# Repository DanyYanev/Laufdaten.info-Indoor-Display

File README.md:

# Laufdaten.info Dust Sensor Indoor Display
Add-on indoor display for your [**laufdaten dust sensor**](https://luftdaten.info/en/home-en/)

If you are contributing to the [**luftdaten.info**](https://luftdaten.info/en/home-en/) project you can build your own indoor weather station and fetch the data off your outdoor sensor.
# How it works
Outside sensor sends information to the Laufdaten servers and to the indoor controller API that displays it on display by your choice. The display controller is connected to your local network with static IP configured from the .ino file (default 192.168.0.50).
The same IP Address you have to add in the outside sensor to send data to the indoor display controller. (More on that in the Configuration Tab) 

*Screenshots from 2.8"(background actually is black)*

# Getting Started
You will need:
  - Working [Laufdaten dust sensor](https://luftdaten.info/en/construction-manual/) **with BME 280 and SDS011**
  - *Another* NodeMCU v3 ESP8266 or ESP-12E
  - *Another* BME 280
  - A display
    - OLED 0.96" I2C interface
    - OLED 1.3" I2C interface
    - LCD TFT 1.44" SPI interface
    - LCD TFT 2.8"  SPI interface with touch
    - LCD TFT 2.8"  SPI interface without touch
    
## Installing
  ##### Setting up the arduino IDE
  - Install the [Arduino IDE](https://www.arduino.cc/en/Main/Software)
  - Add ESP8266 Libraries
    To begin, we’ll need to update the board manager with a custom URL. Open up Arduino, then go to the Preferences (File > Preferences).       Then, towards the bottom of the window, copy this URL into the “Additional Board Manager URLs” text box:

     > http://arduino.esp8266.com/stable/package_esp8266com_index.json
   - Install the following libraries
      - [WifiManager by Ken Taylor](https://github.com/kentaylor/WiFiManager)
      - [Adafruit Sensors](https://github.com/adafruit/Adafruit_Sensor)
      - [Adafruit BME280](https://github.com/adafruit/Adafruit_BME280_Library)
      - LCD
        - [TFT_eSPI by Bodmer](https://github.com/Bodmer/TFT_eSPI)
      - OLED
        - [Driver library for the SSD1306 and SH1106 OLED by ThingPulse](https://github.com/ThingPulse/esp8266-oled-ssd1306)
        
  ##### Connect the hardware for Oled and LCD 1.44"
  - BME280 (I2C)
    - SDA -> D1
    - SDL -> D2
  - OLED (I2C)
    - SDA -> D1
    - SDL -> D2
  - LCD (SPI)
    - TFT_CS -> D8
    - TFT_DC -> D0
    - TFT_RST -> Reset pin
    - TFT_SCL -> D5
    - TFT_SDA -> D7
    - TFT_LED -> +3.3v
    - Make the appropriate changes to User_Setup.h in Bodmer library (by default on Windowns located in Documents/Arduino/libraries/TFT-eSPI/) according to your display. The User_Setup.h file is very well documented.
    - You can find ready User_Setup.h in code folders. For 1.44 if you have screen offset choose different board.
            
  - Buttons (Pin to GND)
    - D6 (Display page changing)
    - D3 (Configuration Mode -Onboard flash button)
  - You can look also schematic pdf in shields folder
  
  ##### Connect the hardware for LCD 2.80"
  - See schematic pdf in shields folder
  
##### Configure the Indoor Display Conroller
  - After uploading the code the controller will run in Configuration Mode automatically. To manually put the controller in config mode use the flash button. 
  - The device tries to connect to the configured WLAN access point. If this does not work, the controller opens an access point with the name "ESP *id*". The ID referes to the ChipID (ex. ESP12345). Connect to the new network, wait a moment until the connection is made. Sometimes it take multiple attempts.
  - Configure using browser
    - Open your browser and type in http://192.168.4.1/. You see the menu site, choose “Configure” and input your credentional.
    - After saving the desired configuration click on **EXIT PORTAL**! Else the configuration won't be saved.
  **OR**
  - Configure using android application. Special thanks to Keneth Taylor.
    - Download the [ESP Connect app](https://play.google.com/store/apps/details?id=au.com.umranium.espconnect) and follow the steps.
  - Oled version is without WiFi menager and you must add wifi SSID and Password in the code.  
  
##### Configure the OutsideSensor
  - Find laufdatens sensor IP Address.
  - Go to its IP Address (ex. 192.168.0.112)
  - Click on Configuration
  - Add the static IP of the indoor display controller 192.168.0.50, (standart router settings from 192.168.0.2 through 192.168.0.99 are not used for DHCP).
  - The path and the port as shown below.

## Shields
  - Kicad and Gerber files are in shields folder.
    - Indoor display
      - Oled 0.96 (Tested)
      - LCD 1.44  (Tested)
      - LCD 2.80  (ESP-12E tested)
      - LCD 2.80  (NodeMCU not tested)
    - Outdoor sensor for better connection between sensors and ESP.

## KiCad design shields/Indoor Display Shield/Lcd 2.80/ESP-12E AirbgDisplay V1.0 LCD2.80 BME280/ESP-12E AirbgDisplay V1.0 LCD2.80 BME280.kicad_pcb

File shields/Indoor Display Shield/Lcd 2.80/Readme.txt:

Buttons on D2 and D6 are not used with touchscreen.
Led on D4 duplicate led on ESP.
PCB can be use with another sensors for air quality BME680 or CCS811.

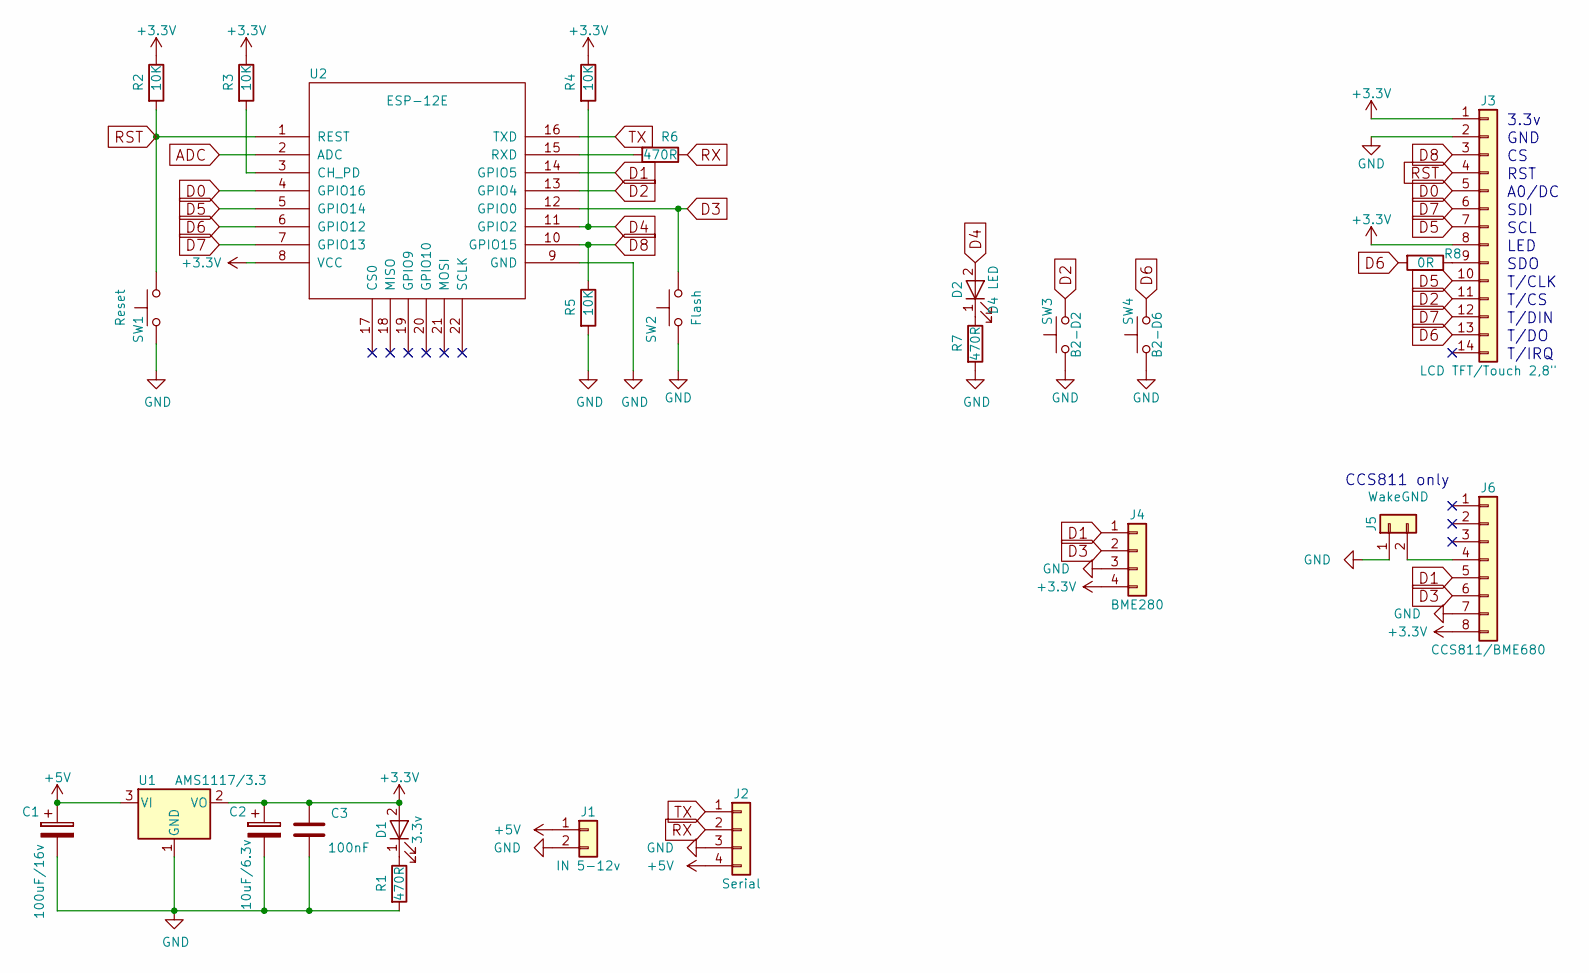
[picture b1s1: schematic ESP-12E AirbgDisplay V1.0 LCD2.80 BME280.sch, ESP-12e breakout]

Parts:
C1: 100uF/16v; C_1812_HandSoldering
C2: 10uF/6.3v; C_1206_HandSoldering
C3: 100nF; C_1206_HandSoldering
D1: 3.3v; LED_1206_HandSoldering
D2: D4 LED; LED_1206_HandSoldering
J1: IN 5-12v; Pin_Header_Straight_1x02_Pitch2.54mm
J2: Serial; Pin_Header_Angled_1x04_Pitch2.54mm
J3: LCD TFT/Touch 2,8\"; Pin_Header_Straight_1x14_Pitch2.54mm
J4: BME280; Pin_Header_Straight_1x04_Pitch2.54mm
J5: WakeGND; Pin_Header_Straight_1x02_Pitch2.54mm
J6: CCS811/BME680; Pin_Header_Straight_1x08_Pitch2.54mm
R1, R6, R7: 470R; R_1206_HandSoldering
R2, R3, R4, R5: 10K; R_1206_HandSoldering
R8: 0R; R_1206_HandSoldering
SW1: Reset; SW_SPST_FSMSM
SW2: Flash; SW_SPST_FSMSM
SW3: B2-D2; SW_SPST_FSMSM
SW4: B2-D6; SW_SPST_FSMSM
U1: AMS1117/3.3; SOT-223-3_TabPin2
U2: ESP-12E; ESP-12E_SMD

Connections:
+3V3: C2.1, C3.1, D1.2 (A), J3.1, J3.8, J4.4, J6.8, R2.1, R3.1, R4.1, U1.2 (VO), U2.8 (VCC)
+5V: C1.1, J1.1, J2.4, U1.3 (VI)
ADC: U2.2 (ADC)
D0: J3.5, U2.4 (GPIO16)
D1: J4.1, J6.5, U2.14 (GPIO5)
D2: J3.11, SW3.2, U2.13 (GPIO4)
D3: J4.2, J6.6, SW2.2, U2.12 (GPIO0)
D4: D2.2 (A), R4.2, U2.11 (GPIO2)
D5: J3.7, J3.10, U2.5 (GPIO14)
D6: J3.13, R8.2, SW4.2, U2.6 (GPIO12)
D7: J3.6, J3.12, U2.7 (GPIO13)
D8: J3.3, R5.1, U2.10 (GPIO15)
GND: C1.2, C2.2, C3.2, J1.2, J2.3, J3.2, J4.3, J5.1, J6.7, R1.2, R5.2, R7.2, SW1.1, SW2.1, SW3.1, SW4.1, U1.1 (GND), U2.9 (GND)
unnamed: D1.1 (K), R1.1
unnamed: D2.1 (K), R7.1
unnamed: J3.9, R8.1
unnamed: J5.2, J6.4
unnamed: R3.2, U2.3 (CH_PD)
unnamed: R6.2, U2.15 (RXD)
RST: J3.4, R2.2, SW1.2, U2.1 (REST)
RX: J2.2, R6.1
TX: J2.1, U2.16 (TXD)

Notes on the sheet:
3.3v
GND
RST
A0/DC
SDI
SCL
LED
SDO
T/CLK
T/CS
T/DIN
T/DO
T/IRQ
CCS811 only

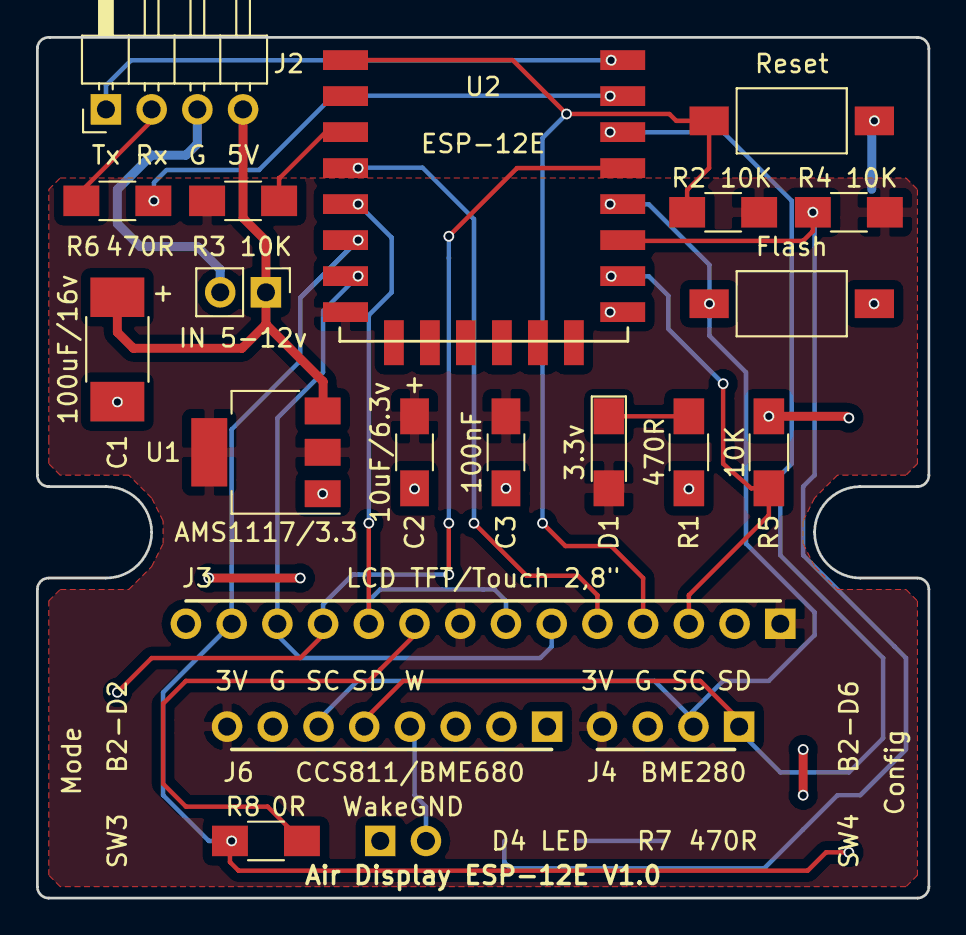
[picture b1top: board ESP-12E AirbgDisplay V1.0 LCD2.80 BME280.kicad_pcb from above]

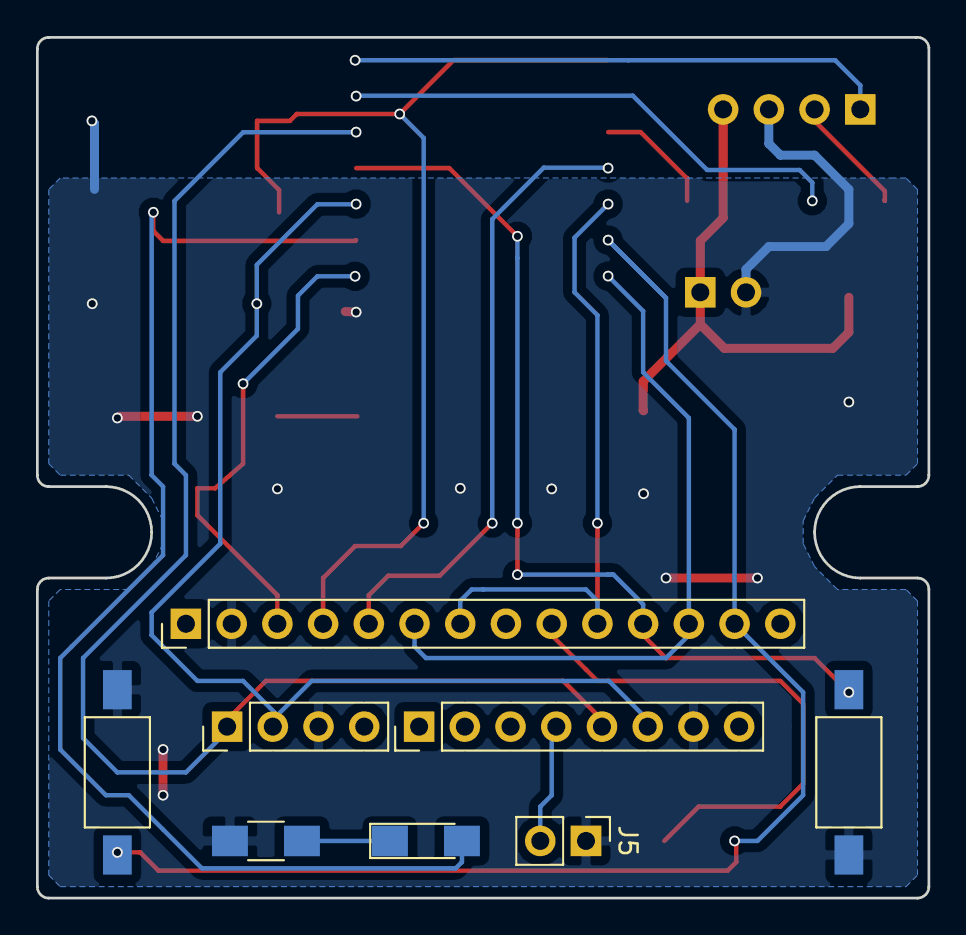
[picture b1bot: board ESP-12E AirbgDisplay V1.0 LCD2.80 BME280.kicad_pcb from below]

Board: 2 copper layers, 49.5 x 47.8 mm, 25 parts (8 on the bottom side), 21 nets.

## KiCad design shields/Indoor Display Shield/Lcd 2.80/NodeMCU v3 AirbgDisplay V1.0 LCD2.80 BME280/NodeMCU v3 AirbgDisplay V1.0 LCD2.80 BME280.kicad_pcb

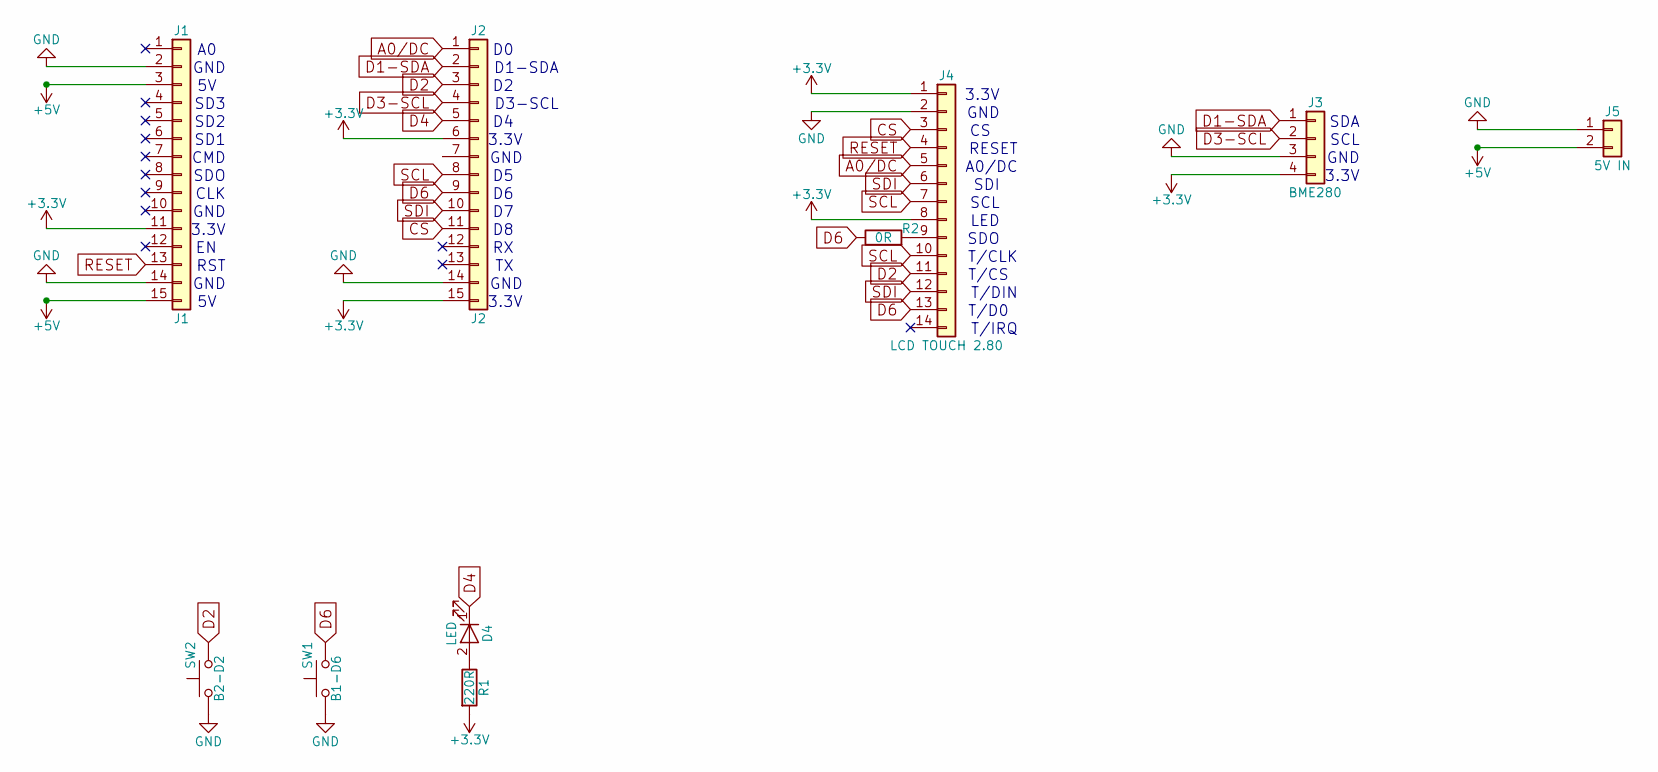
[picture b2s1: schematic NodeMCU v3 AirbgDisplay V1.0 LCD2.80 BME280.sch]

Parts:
D4: LED; LED_1206_HandSoldering
J1: J1; Pin_Header_Straight_1x15_Pitch2.54mm
J2: J2; Pin_Header_Straight_1x15_Pitch2.54mm
J3: BME280; Pin_Header_Straight_1x04_Pitch2.54mm
J4: LCD TOUCH 2.80; Pin_Header_Straight_1x14_Pitch2.54mm
J5: 5V IN; JST_XH_S02B-XH-A_02x2.50mm_Angled
R1: 220R; R_1206_HandSoldering
R2: 0R; R_1206_HandSoldering
SW1: B1-D6; SW_PUSH_6mm_h5mm
SW2: B2-D2; SW_PUSH_6mm_h5mm

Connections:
+3V3: J1.11, J2.6, J2.15, J3.4, J4.1, J4.8, R1.2
+5V: J1.3, J1.15, J5.2
A0/DC: J2.1, J4.5
CS: J2.11, J4.3
D1-SDA: J2.2, J3.1
D2: J2.3, J4.11, SW2.2
D3-SCL: J2.4, J3.2
D4: D4.1 (K), J2.5
D6: J2.9, J4.13, R2.1, SW1.2
GND: J1.2, J1.14, J2.14, J3.3, J4.2, J5.1, SW1.1, SW2.1
unnamed: D4.2 (A), R1.1
unnamed: J4.9, R2.2
RESET: J1.13, J4.4
SCL: J2.8, J4.7, J4.10
SDI: J2.10, J4.6, J4.12

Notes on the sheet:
D1-SDA
D3-SCL
3.3V
GND
SCL
SDA
SD1
SD2
SD3
CMD
SDO
CLK
RST
LED
RESET
A0/DC
SDI
T/CLK
T/CS
T/DIN
T/D0
T/IRQ

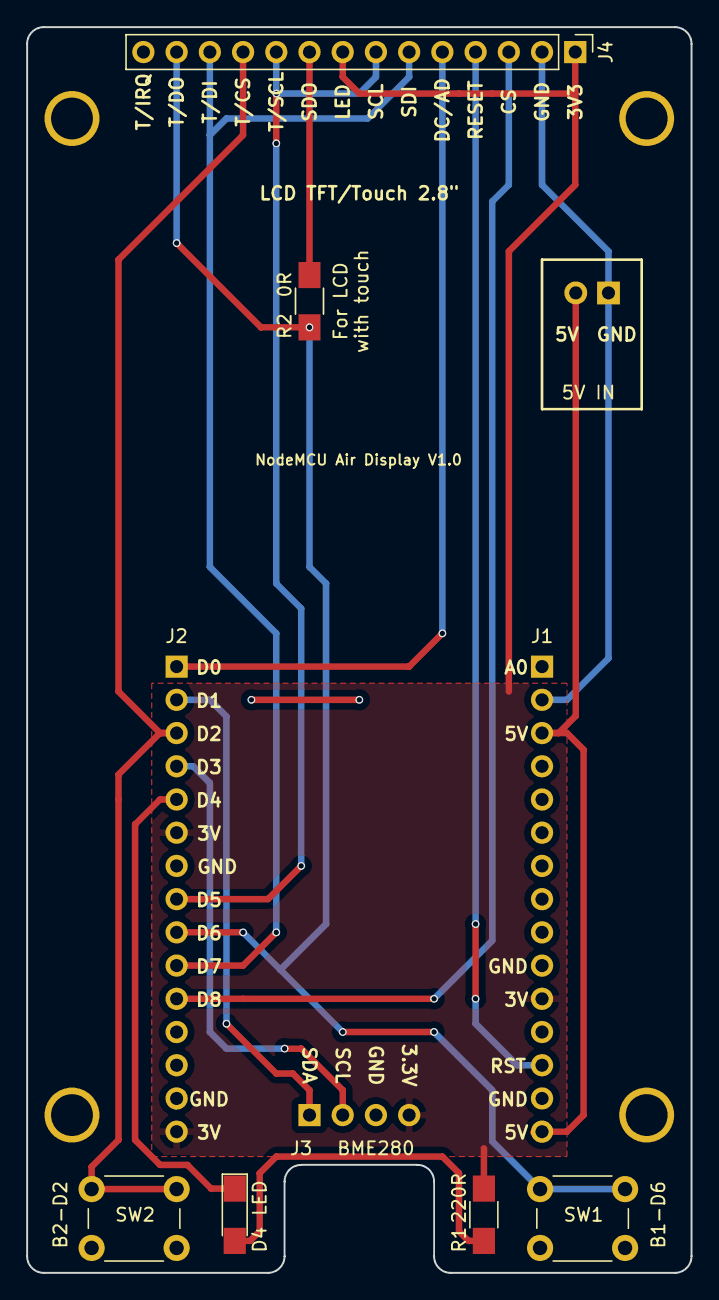
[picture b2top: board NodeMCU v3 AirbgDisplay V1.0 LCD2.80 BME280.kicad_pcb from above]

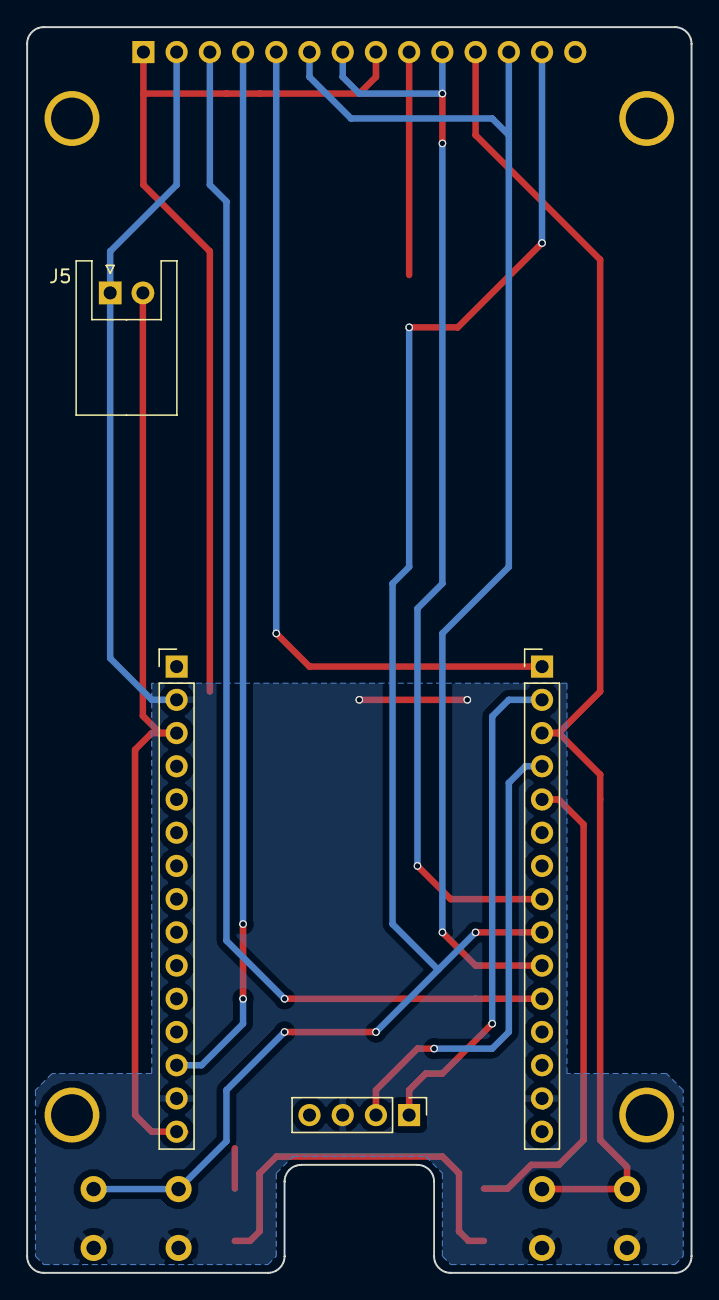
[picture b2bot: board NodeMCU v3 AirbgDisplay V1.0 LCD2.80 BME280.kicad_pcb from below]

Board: 2 copper layers, 50.8 x 95.2 mm, 14 parts (8 on the bottom side), 15 nets.

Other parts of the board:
3mm, 3mm#2, 3mm#3, 3mm#4: 1; SolderWirePad_single_2mmDrill

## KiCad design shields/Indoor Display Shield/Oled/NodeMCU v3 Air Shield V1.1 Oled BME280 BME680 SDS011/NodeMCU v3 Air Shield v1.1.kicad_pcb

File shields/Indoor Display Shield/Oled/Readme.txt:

This shield is for Oled 0.96 and few sensors 
(BME280,BME680 and SDS011).
For this code use only BME280 and 2 buttons.

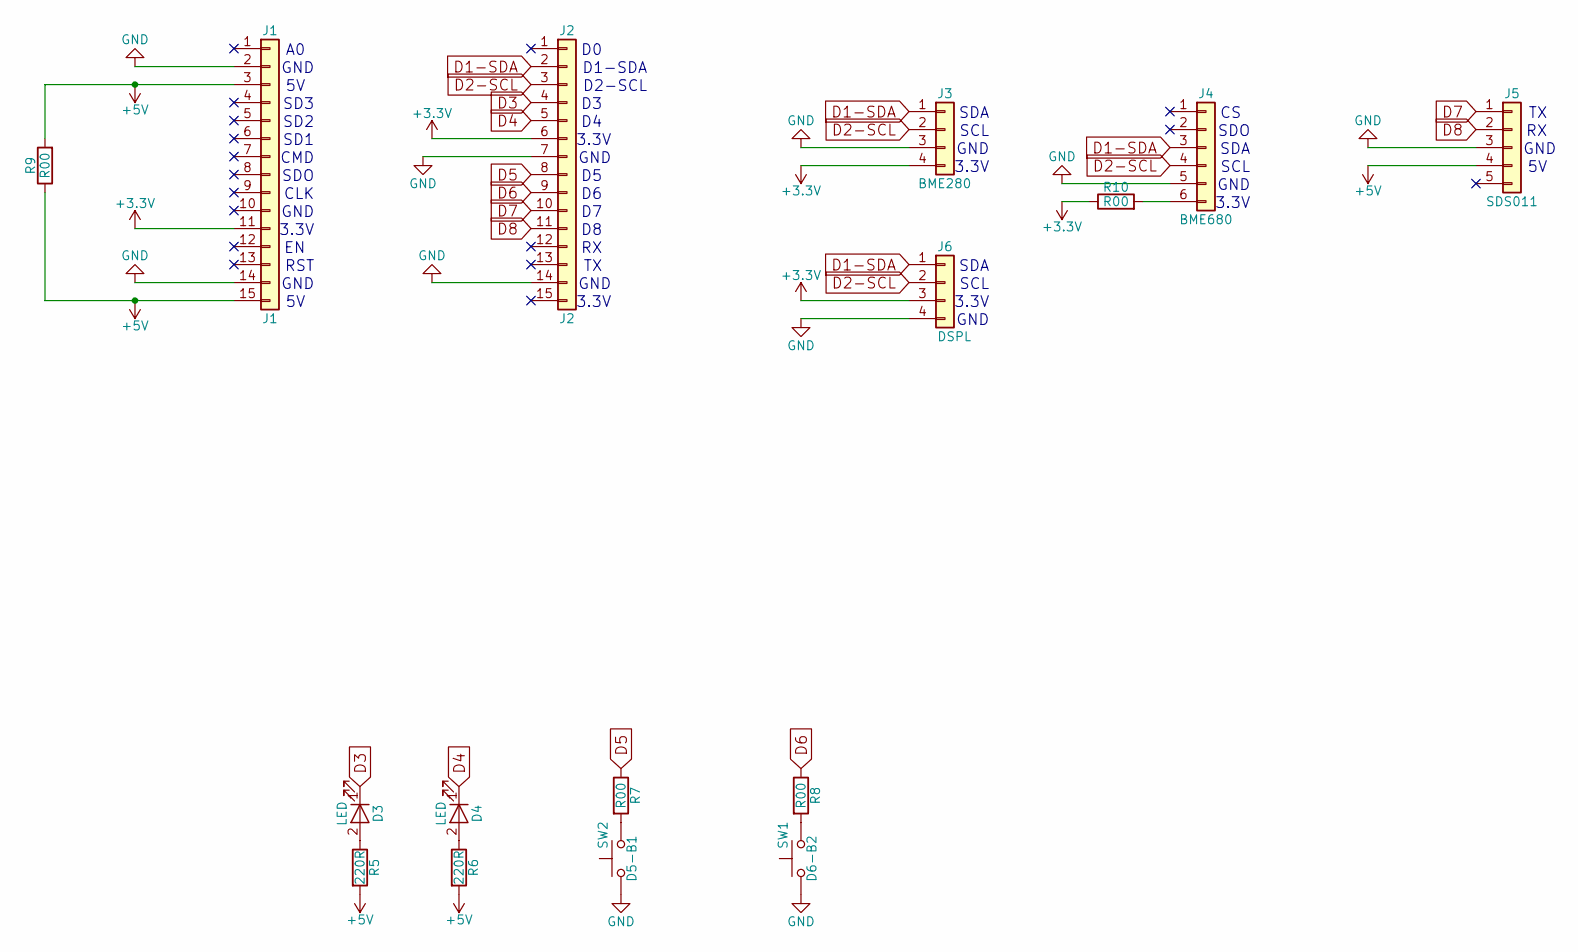
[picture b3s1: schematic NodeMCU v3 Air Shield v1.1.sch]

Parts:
D3, D4: LED; LED_1206_HandSoldering
J1: J1; Pin_Header_Straight_1x15_Pitch2.54mm
J2: J2; Pin_Header_Straight_1x15_Pitch2.54mm
J3: BME280; Pin_Header_Straight_1x04_Pitch2.54mm
J4: BME680; Pin_Header_Straight_1x06_Pitch2.54mm
J5: SDS011; JST_XH_S05B-XH-A_05x2.50mm_Angled
J6: DSPL; Pin_Header_Straight_1x04_Pitch2.54mm
R5, R6: 220R; R_1206_HandSoldering
R7, R8, R9, R10: R00; WireConnection_1.00mmDrill
SW1: D6-B2; SW_PUSH_6mm
SW2: D5-B1; SW_PUSH_6mm

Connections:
+3V3: J1.11, J2.6, J3.4, J6.3, R10.1
+5V: J1.3, J1.15, J5.4, R5.2, R6.2, R9.1, R9.2; also elsewhere on the board
D1-SDA: J2.2, J3.1, J4.3, J6.1
D2-SCL: J2.3, J3.2, J4.4, J6.2
D3: D3.1 (K), J2.4
D4: D4.1 (K), J2.5
D5: J2.8, R7.1
D6: J2.9, R8.1
D7: J2.10, J5.1
D8: J2.11, J5.2
GND: J1.2, J1.14, J2.7, J2.14, J3.3, J4.5, J5.3, J6.4, SW1.1, SW2.1; also elsewhere on the board
unnamed: D3.2 (A), R5.1
unnamed: D4.2 (A), R6.1
unnamed: J4.6, R10.2
unnamed: R7.2, SW2.2
unnamed: R8.2, SW1.2

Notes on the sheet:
D1-SDA
D2-SCL
3.3V
GND
SCL
SDO
SDA
SD1
SD2
SD3
CMD
CLK
RST

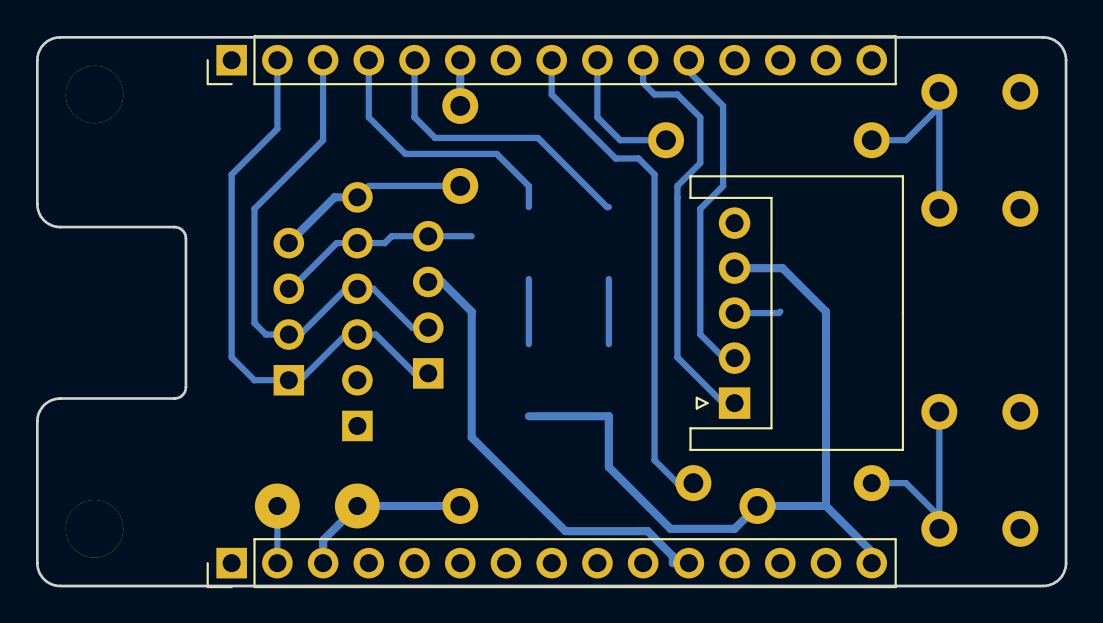
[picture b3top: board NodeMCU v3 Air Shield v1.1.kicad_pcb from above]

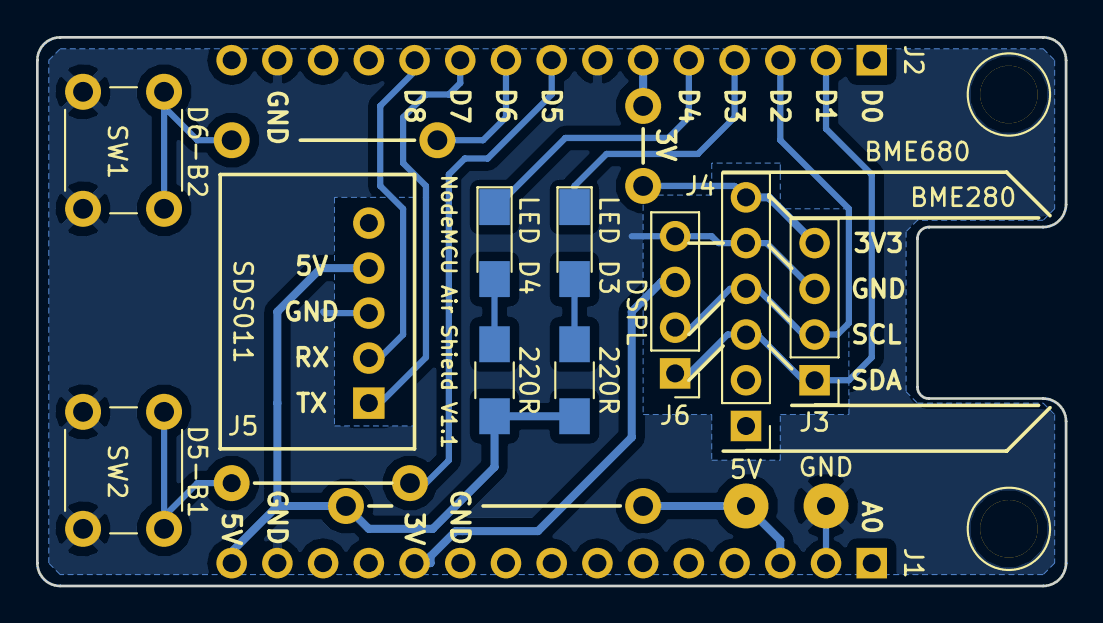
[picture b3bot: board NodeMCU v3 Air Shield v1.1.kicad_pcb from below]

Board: 2 copper layers, 57.1 x 30.5 mm, 19 parts (13 on the bottom side), 16 nets.

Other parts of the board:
3mm, 3mm#2: 1pin
5V: GND; SolderWirePad_2x_1mmDrill

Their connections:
+5V: 5V.1; also elsewhere on the board
GND: 5V.1; also elsewhere on the board

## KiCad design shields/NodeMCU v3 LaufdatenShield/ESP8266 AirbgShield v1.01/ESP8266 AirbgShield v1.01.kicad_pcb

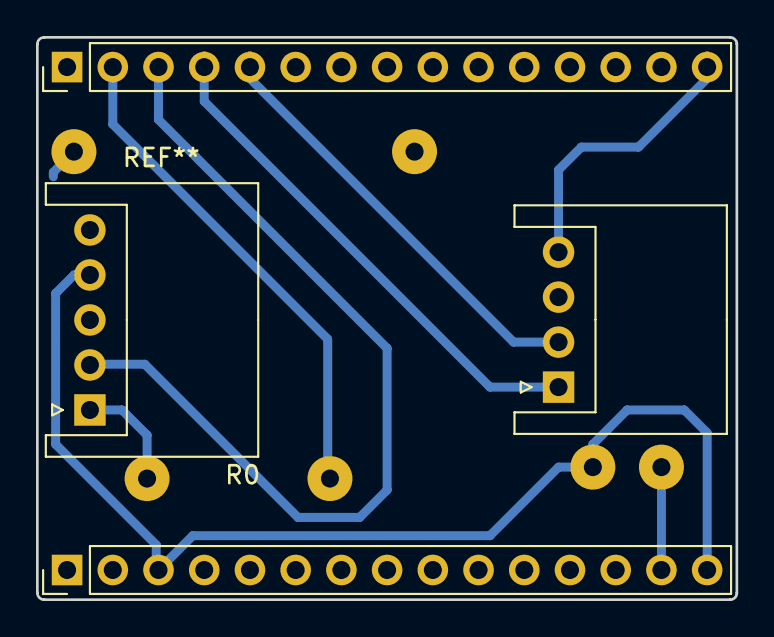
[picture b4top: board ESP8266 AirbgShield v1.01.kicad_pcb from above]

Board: 2 copper layers, 38.9 x 31.2 mm, 6 parts (0 on the bottom side), 8 nets.

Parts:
J1, J2: P15; Pin_Header_Straight_1x15_Pitch2.54mm
J3: SDS011; JST_XH_S05B-XH-A_05x2.50mm_Angled
J4: BME280; JST_XH_S04B-XH-A_04x2.50mm_Angled
Power: WireConnection_1mmDrill; WireConnection_1.00mmDrill
R0: J; WireConnection_1.00mmDrill

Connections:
+3V3: J2.15, J4.4
+5V: J1.3, J1.15, J3.4, Power.1
GND: J1.14, J2.14, J3.3, J4.3, Power.2
I2C_SCL: J2.5, J4.2
I2C_SDA: J2.4, J4.1
unnamed: J2.2, R0.1
RX: J2.3, J3.2
TX: J3.1, R0.2

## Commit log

2018-04-02 Readme with dependencies
2018-04-02 Added code and shields
2018-04-02 readme fixes and updated dependencies
2018-04-02 Now parsing flexable jsons
2018-04-02 Flexible jason parsing
2018-04-04 Some cosmetics on lcd screen
2018-04-06 Add schematic
2018-04-06 Change folders
2018-04-06 Add pictures
2018-04-06 Add schematics
2018-04-06 Lcd 1.44 r07
2018-04-06 Static IP
2018-04-07 code fixing
2018-04-07 Add bme280
2018-04-08 Add Oled shield
2018-04-08 Oled pictures
2018-04-29 I2C fix
2018-12-12 Some fixes
2018-12-15 New pcb and code
2018-12-15 IP fix
2018-12-20 Shield pictures
2018-12-21 Gerber files add
2018-12-23 Shematic
2018-12-23 Code fix
